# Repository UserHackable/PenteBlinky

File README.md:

## PentaBlinky 

### Board dimensions

* (160000, 90000) original units
* (1.6000, 0.9000) inches
* (40.6400, 22.8600) mm

| Front | Back |
| --- | --- |
|  |  |

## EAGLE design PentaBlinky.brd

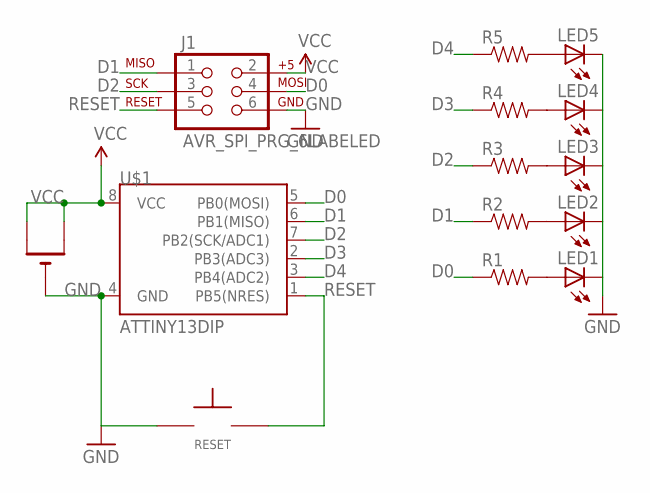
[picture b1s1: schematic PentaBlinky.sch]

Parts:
J1: AVR_SPI_PRG_6LABELED; 2X3-NS
LED1, LED2, LED3, LED4, LED5: LED5MM
R1, R2, R3, R4, R5: RESISTORAXIAL-0.3; AXIAL-0.3
RESET: SPST_NO; TAC_SPST_NO
U$1: ATTINY13DIP; DIP08
U$4: BATT_GEN; AA-AAA

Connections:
D0: J1.4 (MOSI), R1.P$1 (1), U$1.5 (PB0(MOSI))
D1: J1.1 (MISO), R2.P$1 (1), U$1.6 (PB1(MISO))
D2: J1.3 (SCK), R3.P$1 (1), U$1.7 (PB2(SCK/ADC1))
D3: R4.P$1 (1), U$1.2 (PB3(ADC3))
D4: R5.P$1 (1), U$1.3 (PB4(ADC2))
GND: J1.6 (GND), LED1.K (C), LED2.K (C), LED3.K (C), LED4.K (C), LED5.K (C), RESET.P$1, U$1.4 (GND), U$4.-
unnamed: LED1.A, R1.P$2 (2)
unnamed: LED2.A, R2.P$2 (2)
unnamed: LED3.A, R3.P$2 (2)
unnamed: LED4.A, R4.P$2 (2)
unnamed: LED5.A, R5.P$2 (2)
RESET: J1.5 (RST), RESET.P$2, U$1.1 (PB5(NRES))
VCC: J1.2 (V+), U$1.8 (VCC), U$4.+, U$4.++ (+1)

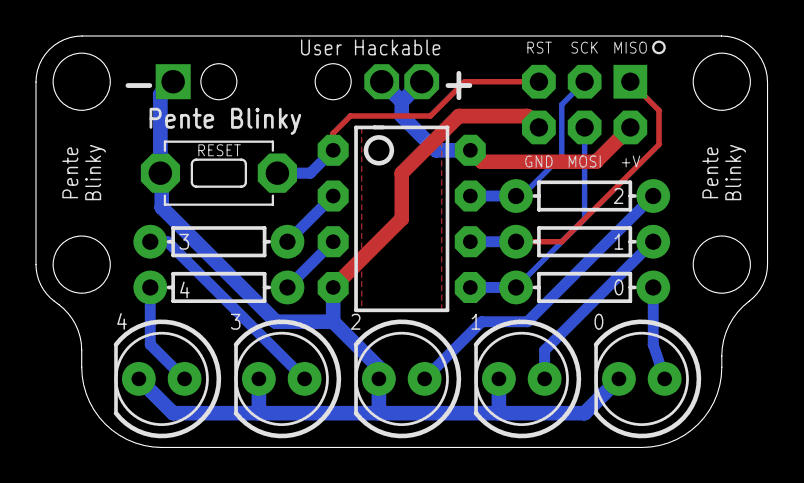
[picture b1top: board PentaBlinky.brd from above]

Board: 2 copper layers, 40.6 x 22.9 mm, 14 parts (0 on the bottom side), 13 nets.

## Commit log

2016-04-06 fixing back traces
2016-04-07 from Makefile

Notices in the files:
parts and their libraries:
SparkFun-DigitalIC: Licensing: Creative Commons ShareAlike 4.0 International - https://creativecommons.org/licenses/by-sa/4.0
